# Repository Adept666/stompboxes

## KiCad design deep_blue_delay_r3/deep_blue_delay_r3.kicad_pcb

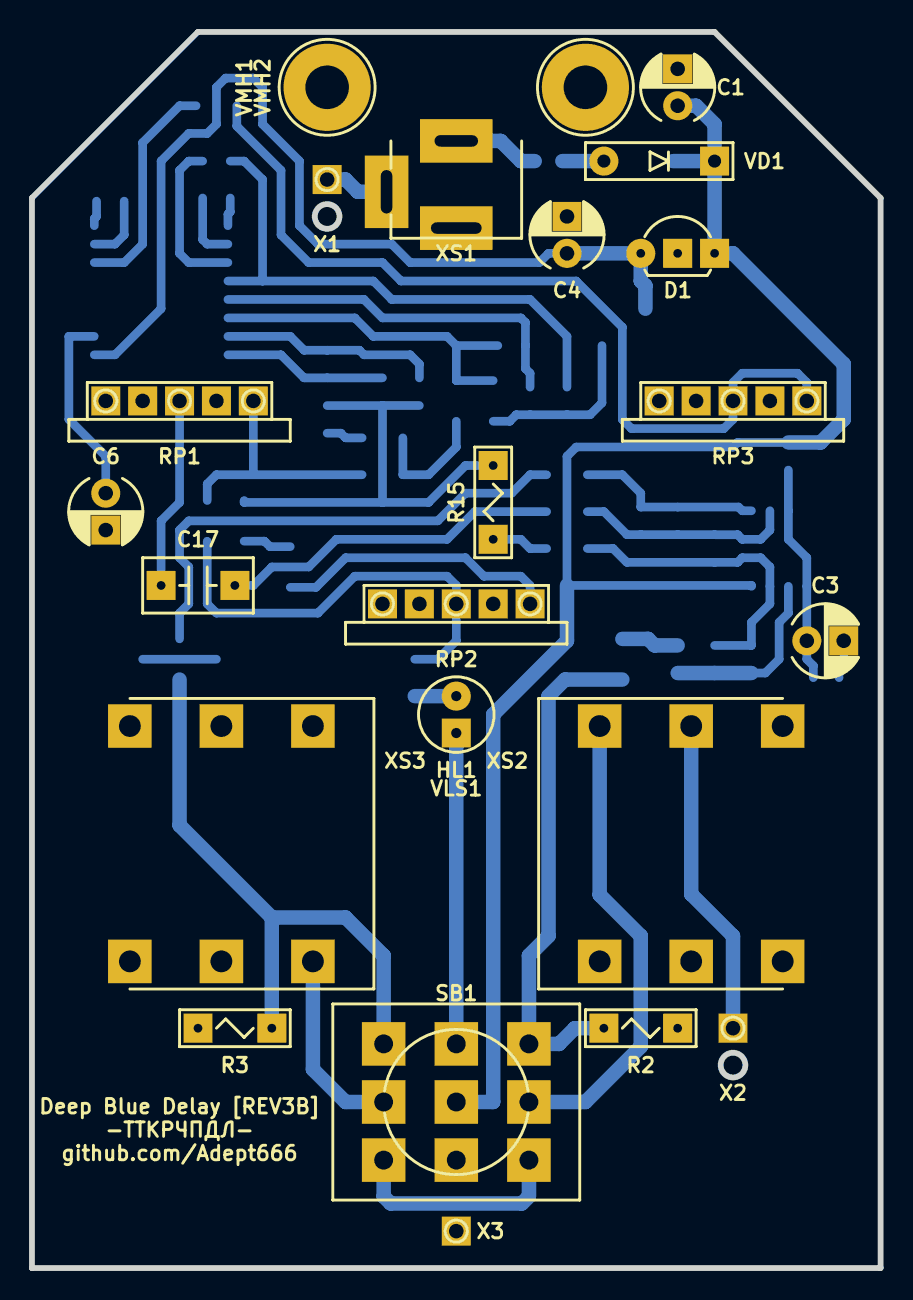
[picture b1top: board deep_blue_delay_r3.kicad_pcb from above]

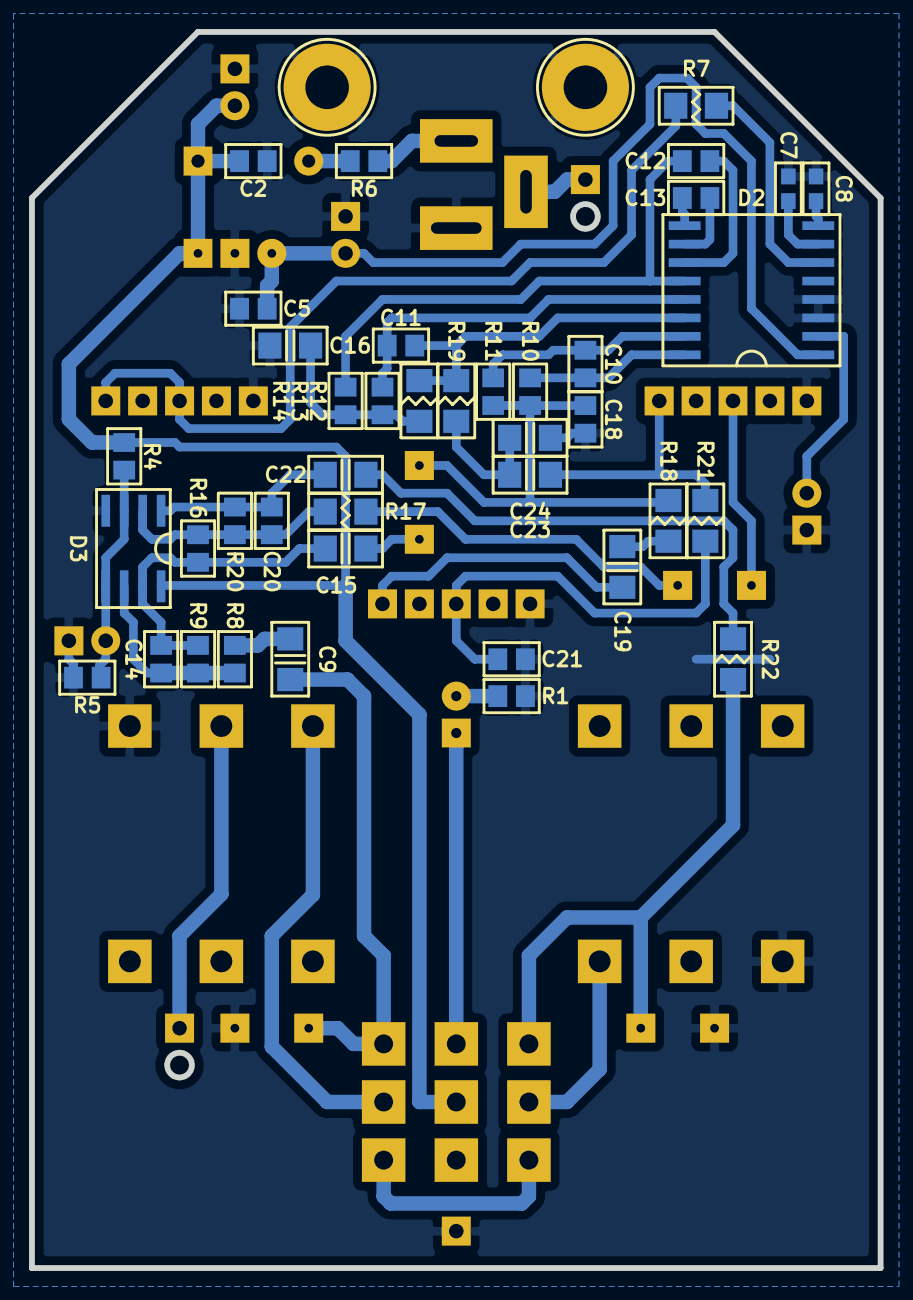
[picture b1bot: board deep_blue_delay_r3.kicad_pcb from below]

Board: 2 copper layers, 58.4 x 85.1 mm, 66 parts (40 on the bottom side), 44 nets.

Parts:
C1: 107; CP-RADIAL-D05.0-P02.0-CLS
C2, C5, C12, C13: 104; C-SM-0805
C3, C4, C6: 476; CP-RADIAL-D05.0-P02.0-CLS
C7, C8: 104; C-SM-0603
C9, C19: 223; C-SM-1206
C10, C11: 222; C-SM-0805
C14: 470; C-SM-0805
C15, C22, C23: 105; C-SM-1206
C16: 153; C-SM-1206
C17: 105; C-DISK-D04.2-T03.0-P05.08-d0.5
C18: 472; C-SM-0805
C20: 101; C-SM-0805
C21: 473; C-SM-0805
C24: 103; C-SM-1206
D1: 78L05; P-TO-92-OUT-GND-IN
D2: 8970; P-SO-16W
D3: 5532; P-SO-08
GB1: PP3; B-PP3-HV
HL1: FYL-5013UWC; LED-ROUND-05.0-UNI-SH-SPACER
R1, R4, R5, R10, R11, R13, R14: 103; R-SM-0805
R2: 105; R-MFR-12
R3: 104; R-MFR-12
R6: 330; R-SM-0805
R7: 272; R-SM-1206
R8: 184; R-SM-0805
R9: 364; R-SM-0805
R12, R17: 203; R-SM-1206
R15: 103; R-MFR-12
R16: 223; R-SM-0805
R18: 512; R-SM-1206
R19, R22: 102; R-SM-1206
R20: 123; R-SM-0805
R21: 202; R-SM-1206
RP1, RP2, RP3: B50K; RP-PDB181-K-F-PCB-RND
SB1: PBS-24-302SP; SW-PBS-24-302SP
VD1: 5817; P-DO-41
VE1: B013; B013_deep_blue_delay_r3a
VLS1: BR-17.8; VLS-BR
VMH1, VMH2: DI5M3x20; VMH-STA-DA5
X1: +; CON-PAD-S-1.0-2.0
X2: -; CON-PAD-S-1.0-2.0
X3: COM; CON-PAD-S-1.0-2.0
XS1: DC-005; CON-DC-005
XS2, XS3: PJ-644C; CON-PJ-644C

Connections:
/IN-CON: SB1.COM3, XS2.T
/IN-SCH: C9.1, R2.2, SB1.NO3
/LED: HL1.A, SB1.NO2
/OUT-CON: SB1.COM1, XS3.T
/OUT-SCH: R3.2, R22.2, SB1.NO1
/PP3-NEG: X2.1, XS2.R
/PP3-POS: X1.1, XS1.SN
COM: C1.-, C2.2, C3.-, C4.-, C5.2, C6.-, C7.1, C8.1, C16.2, C18.2, C21.2, C24.2, D1.GND, D2.3, D2.4, D3.4, R1.1, R2.1, R3.1, R5.1, RP1.1, RP2.1, RP3.1, VMH1.0, VMH2.0, X3.1, XS1.C, XS2.S, XS3.S
unnamed: C6.+, D2.2
unnamed: C7.2, D2.7
unnamed: C8.2, D2.8
unnamed: C9.2, R8.1
unnamed: C10.1, D2.16, R10.1
unnamed: C10.2, D2.15, R11.1
unnamed: C11.1, D2.14, R12.1, R19.1
unnamed: C11.2, D2.13, R13.1
unnamed: C12.1, D2.12, R14.1
unnamed: C12.2, D2.11
unnamed: C13.1, D2.10
unnamed: C13.2, D2.9
unnamed: C14.1, D3.6, R8.2, R9.1
unnamed: C14.2, C15.1, D3.7, R9.2, R16.1
unnamed: C15.2, R15.2
unnamed: C16.1, R12.2, R13.2, R14.2
unnamed: C17.1, R17.1
unnamed: C17.2, RP1.2
unnamed: C18.1, R10.2, R11.2, R15.1, R18.2
unnamed: C19.1, R18.1
unnamed: C19.2, RP2.3
unnamed: C20.1, D3.2, R16.2, R17.2, R20.1
unnamed: C20.2, C22.1, D3.1, R20.2
unnamed: C21.1, R21.1, RP2.2
unnamed: C22.2, R22.1
unnamed: C23.1, R21.2, RP1.3
unnamed: C23.2, C24.1, R19.2
unnamed: D2.6, R7.2
unnamed: HL1.C, R1.2
unnamed: R6.1, XS1.S
unnamed: R6.2, VD1.A
unnamed: R7.1, RP3.2, RP3.3
unnamed: SB1.NC1, SB1.NC3
V: C1.+, C2.1, D1.IN, D3.8, R4.2, SB1.COM2, VD1.C
VA: C4.+, C5.1, D1.OUT, D2.1
VB: C3.+, D3.3, D3.5, R4.1, R5.2

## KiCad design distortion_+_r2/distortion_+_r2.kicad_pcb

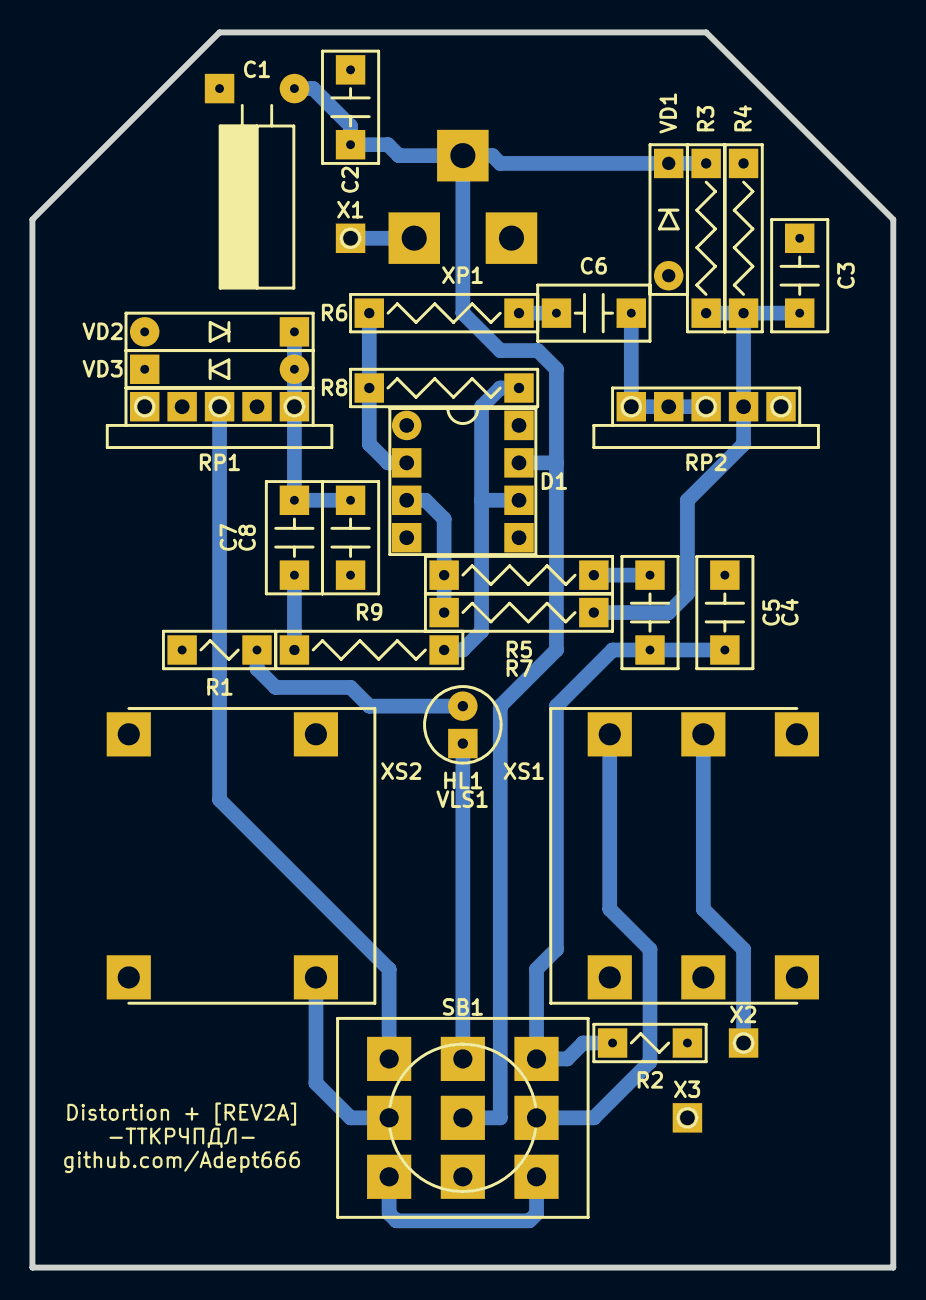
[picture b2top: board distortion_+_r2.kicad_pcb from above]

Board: 2 copper layers, 58.4 x 83.8 mm, 34 parts (0 on the bottom side), 20 nets.

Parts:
C1: 107; CP-RADIAL-D05.0-P02.0-d0.5-L11-HU
C2: 104; C-DISK-D04.2-T03.0-P05.08-d0.5
C3, C7: 105; C-DISK-D04.2-T03.0-P05.08-d0.5
C4, C8: 102; C-DISK-D04.2-T03.0-P05.08-d0.5
C5: 103; C-DISK-D04.2-T03.0-P05.08-d0.5
C6: 473; C-DISK-D04.2-T03.0-P05.08-d0.5
D1: 741; P-DIP-08
GB1: PP3; B-PP3-HV
HL1: FYL-5013UWC; LED-ROUND-05.0-UNI-SH-SPACER
R1: 103; R-MFR-12
R2: 105; R-MFR-12
R3, R4, R7, R8: 105; R-MFR-25
R5, R9: 103; R-MFR-25
R6: 472; R-MFR-25
RP1: A10K; RP-PDB181-K-F-PCB
RP2: C1M; RP-PDB181-K-F-PCB
SB1: PBS-24-302SP; SW-PBS-24-302SP
VD1: 400x; P-DO-41
VD2, VD3: 34A; P-DO-7
VE1: B013; B013_distortion_+_r2a
VLS1: BR-17.8; VLS-BR
X1: +; CON-PAD-S-1.0-2.0
X2: -; CON-PAD-S-1.0-2.0
X3: COM; CON-PAD-S-1.0-2.0
XP1: 722RA; CON-(L)7X2RA(H)
XS1: NYS215; CON-NYS-215
XS2: NYS2152; CON-NYS-2152

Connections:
/IN-CON: SB1.COM3, XS1.T
/IN-SCH: C4.1, C5.1, R2.2, SB1.NO3
/LED: HL1.A, SB1.NO2
/OUT-CON: SB1.COM1, XS2.T
/OUT-SCH: RP1.2, SB1.NO1
/PP3-NEG: X2.1, XS1.R
/PP3-POS: X1.1, XP1.SN
COM: C1.-, C2.2, C3.2, C4.2, C8.2, D1.4, R1.1, R2.1, R4.1, RP1.1, RP1.NC2, RP2.3, VD1.A, VD2.A, VD3.C, X3.1, XP1.C, XS1.S, XS2.S
unnamed: C5.2, R5.1
unnamed: C6.1, RP2.1, RP2.2, RP2.NC1
unnamed: C6.2, R6.1
unnamed: C7.1, R9.2
unnamed: C7.2, C8.1, RP1.3, VD2.C, VD3.A
unnamed: D1.2, R6.2, R8.1
unnamed: D1.3, R5.2, R7.1
unnamed: D1.6, R8.2, R9.1
unnamed: HL1.C, R1.2
unnamed: SB1.NC1, SB1.NC3
V: C1.+, C2.1, D1.7, R3.2, SB1.COM2, VD1.C, XP1.S
VA: C3.1, R3.1, R4.2, R7.2, RP2.NC2

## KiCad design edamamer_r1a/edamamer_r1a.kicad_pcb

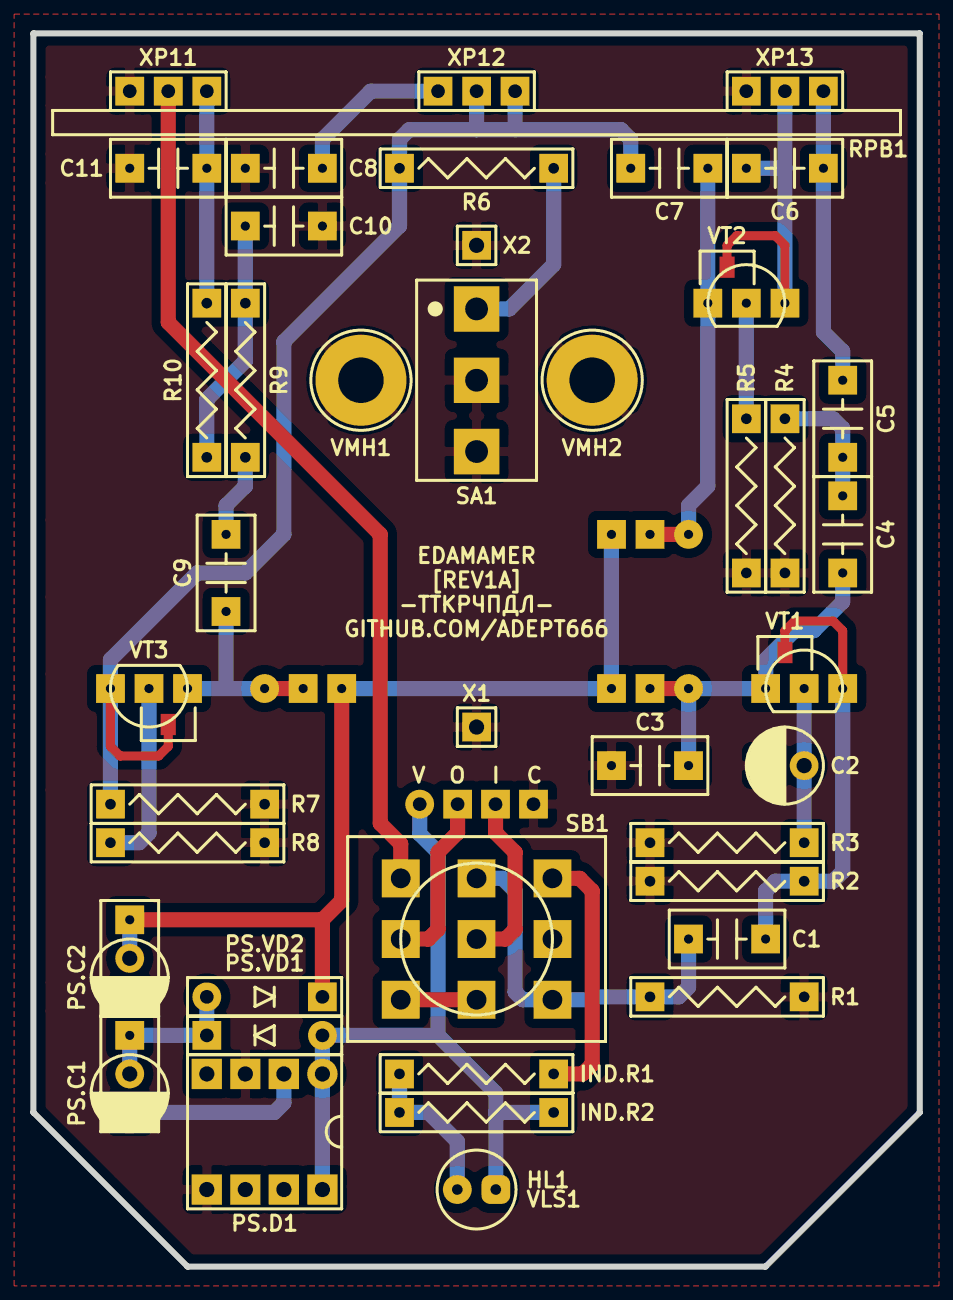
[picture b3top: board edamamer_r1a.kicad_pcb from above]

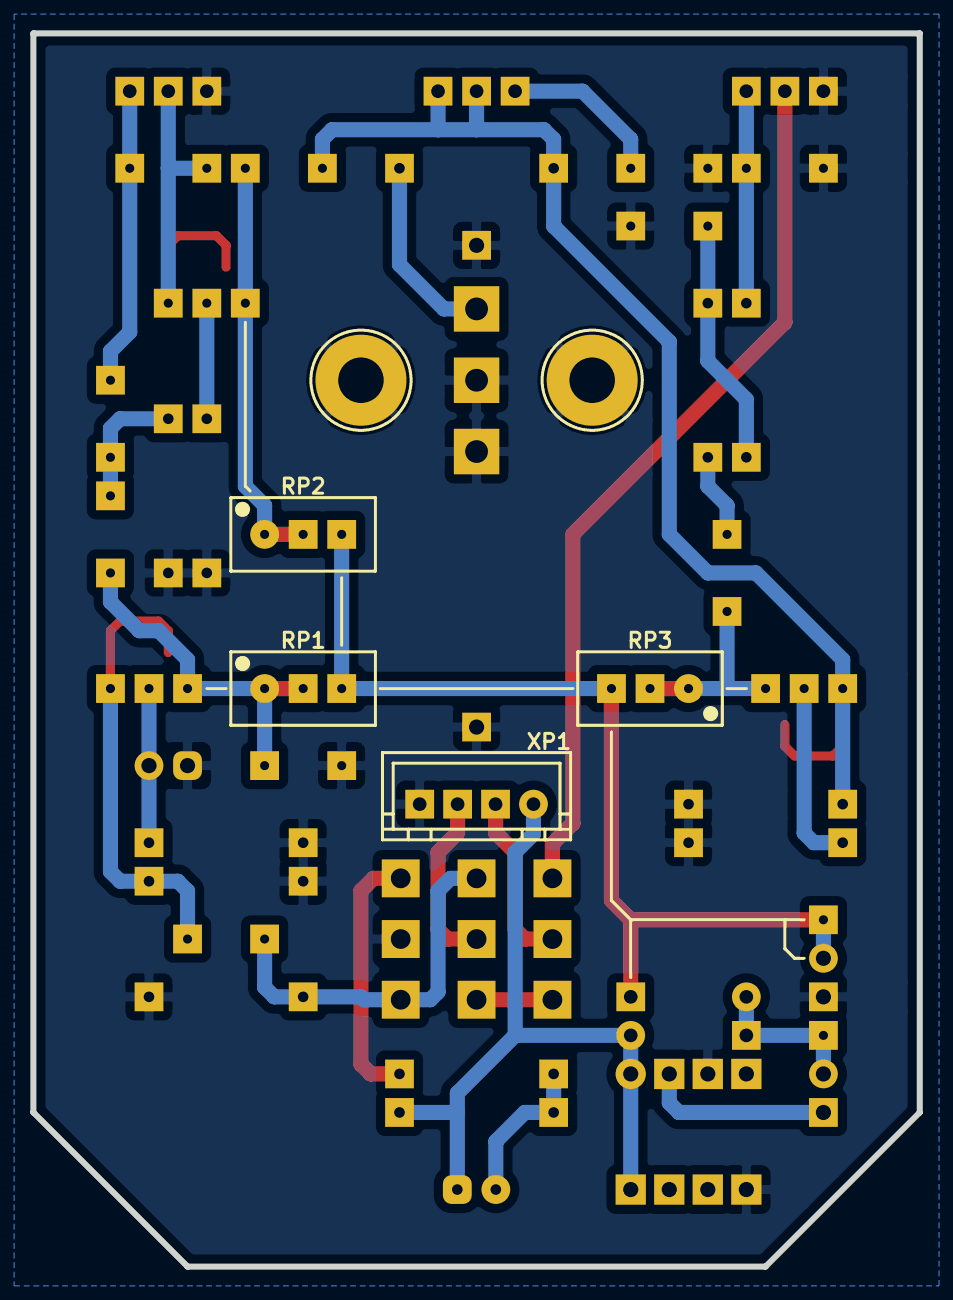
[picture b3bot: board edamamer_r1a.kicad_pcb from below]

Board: 2 copper layers, 58.4 x 81.3 mm, 46 parts (4 on the bottom side), 28 nets.

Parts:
C1: 223; C-DISK-D04.2-T03.0-P05.08-d0.5
C2: 336; CP-RADIAL-D05.0-P02.0-CLS
C3, C6: 471; C-DISK-D04.2-T03.0-P05.08-d0.5
C4, C5, C8: 472; C-DISK-D04.2-T03.0-P05.08-d0.5
C7, C9: 103; C-DISK-D04.2-T03.0-P05.08-d0.5
C10, C11: 332; C-DISK-D04.2-T03.0-P05.08-d0.5
HL1: FYL-5013URC; LED-ROUND-05.0-UNI-SH-SPACER-PNL-5.3
IND.R1: 472; R-MFR-25
IND.R2: X; R-MFR-25
PS.C1, PS.C2: 105; C-DISK-D04.2-T03.0-P05.08-d0.5-OR-CP-RADIAL-D05.0-P02.0-CLS
PS.D1: 7660S; P-DIP-08
PS.VD1, PS.VD2: 400x; P-DO-41
R1, R2: 105; R-MFR-25
R3: 152; R-MFR-25
R4, R7: 474; R-MFR-25
R5: 272; R-MFR-25
R6: 124; R-MFR-25
R8: 221; R-MFR-25
R9, R10: 123; R-MFR-25
RP1, RP2: 100K; RP-3296W
RP3: 50K; RP-3296W
RPB1: A100K-A500K-A500K; RPB-1590N1-18-3x17-1.6-PNL-7.4-2.8
SA1: MTS-102-A2; SW-MTS-102-A2-3.0-PNL-6.0
SB1: PBS-24-302SP; SW-PBS-24-302SP-2.5-PNL-13.0
VE1: 1590N1; 1590N1_A1
VLS1: BR-12.7; VLS-BR
VMH1, VMH2: DI5M3x18; VMH-STA-DA5-PNL-3.0
VT1, VT2: J201; P-SOT-23-D-S-G-OR-TO-92-D-S-G
VT3: 5457; P-SOT-23-D-S-G-OR-TO-92-D-S-G
X1, X2: COM; CON-PAD-S-1.0-1.9
XB1: 1590N1 Connector Board; XB-1590N1
XP1: B4B-XH-A; CON-XH-B4B-A

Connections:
/IN-CIR: C1.1, R1.2, SB1.NC3, SB1.NO2
/IN-CON: SB1.COM2, XP1.3
/LED: IND.R1.1, SB1.NO3
/OUT-CIR: RPB1.12, SB1.NO1
/OUT-CON: SB1.COM1, XP1.2
COM: C2.-, C3.2, C8.2, C10.2, C11.2, PS.C2.-, PS.D1.3, PS.D1.5, R1.1, R2.1, R3.1, R4.1, R5.1, R7.1, R8.1, RPB1.11, RPB1.31, SA1.COM, SA1.NO, SB1.COM3, VMH1.0, VMH2.0, X1.1, X2.1, XP1.4
unnamed: C1.2, R2.2, VT1.G
unnamed: C2.+, R3.2, VT1.S
unnamed: C3.1, C4.1, RP1.1, RP1.2, VT1.D
unnamed: C4.2, C5.1, R4.2
unnamed: C5.2, C6.1, RPB1.33
unnamed: C6.2, RPB1.32, VT2.G
unnamed: C7.1, RP2.1, RP2.2, VT2.D
unnamed: C7.2, R6.2, R7.2, RPB1.22, RPB1.23, VT3.G
unnamed: C8.1, RPB1.21
unnamed: C9.1, RP3.1, RP3.2, VT3.D
unnamed: C9.2, R9.1
unnamed: C10.1, R9.2, R10.1
unnamed: C11.1, R10.2, RPB1.13
unnamed: HL1.C, IND.R1.2, IND.R2.1
unnamed: PS.C1.+, PS.VD1.C, PS.VD2.A
unnamed: PS.C1.-, PS.D1.2
unnamed: R5.2, VT2.S
unnamed: R6.1, SA1.NC
unnamed: R8.2, VT3.S
unnamed: SB1.NC1, SB1.NC2
V: HL1.A, IND.R2.2, PS.D1.1, PS.D1.8, PS.VD1.A, XP1.1
VA: PS.C2.+, PS.VD2.C, RP1.3, RP2.3, RP3.3

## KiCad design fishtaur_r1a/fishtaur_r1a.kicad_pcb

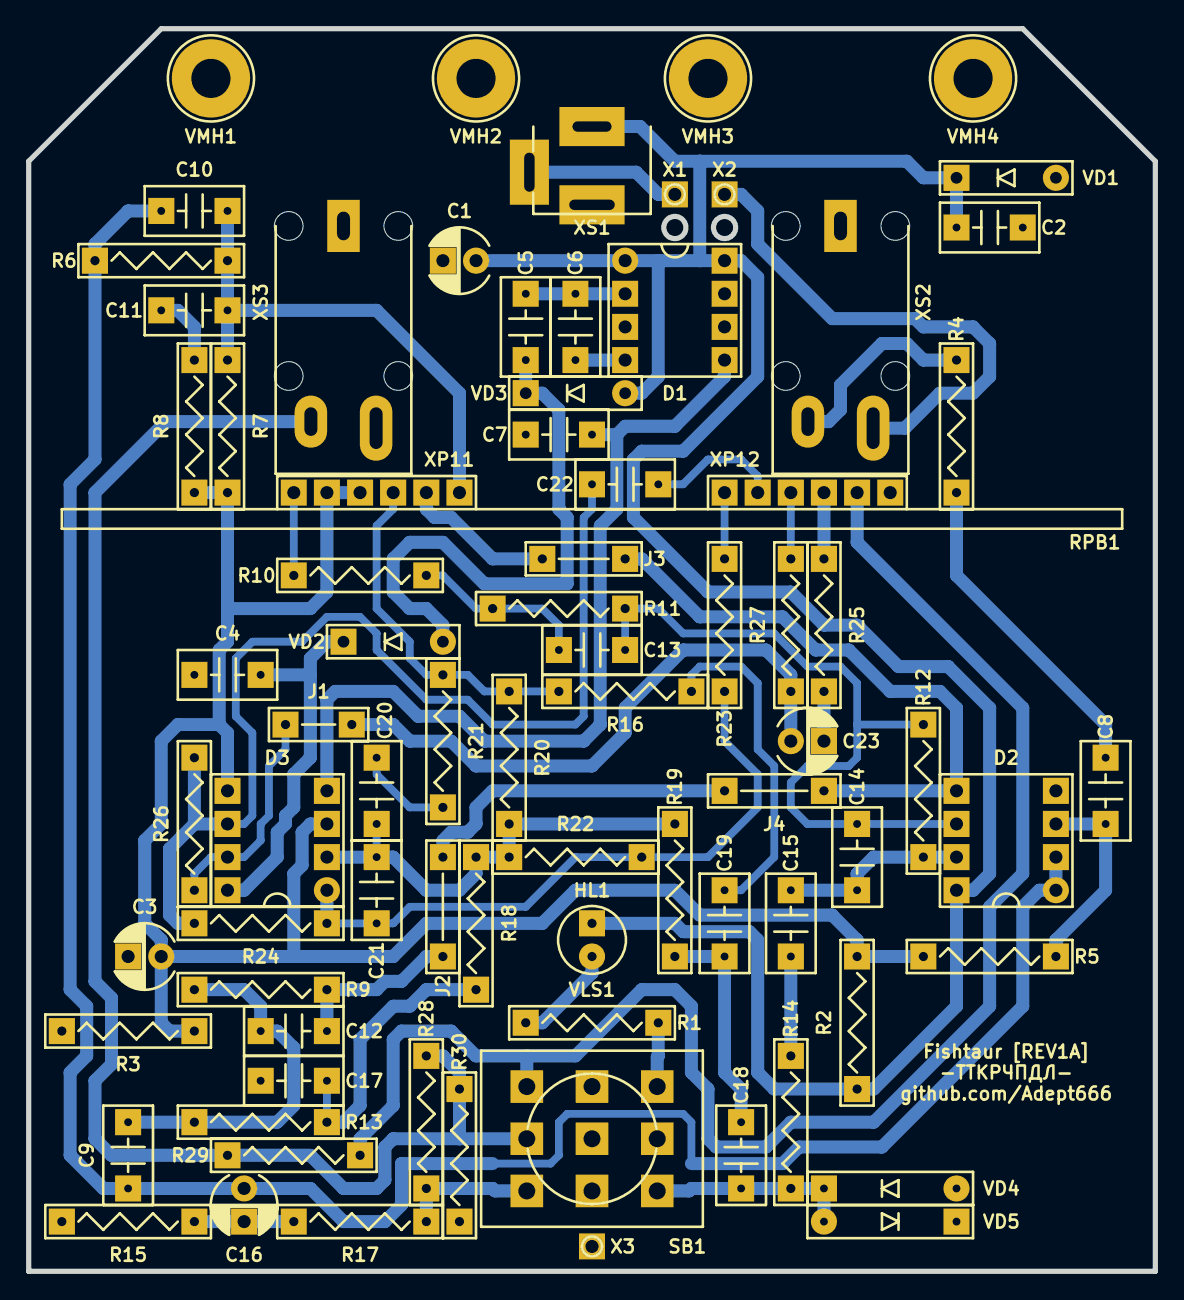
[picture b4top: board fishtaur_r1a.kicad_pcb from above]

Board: 2 copper layers, 86.4 x 95.3 mm, 81 parts (0 on the bottom side), 44 nets.

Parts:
C1, C3: 476; CP-RADIAL-D05.0-P02.0-CLS
C2, C8, C9: 104; C-DISK-D04.2-T03.0-P05.08-d0.5
C4, C5, C6, C7, C15, C17, C18: 105; C-DISK-D04.2-T03.0-P05.08-d0.5
C10, C12: 683; C-DISK-D04.2-T03.0-P05.08-d0.5
C11: 334; C-DISK-D04.2-T03.0-P05.08-d0.5
C13: 823; C-DISK-D04.2-T03.0-P05.08-d0.5
C14: 391; C-DISK-D04.2-T03.0-P05.08-d0.5
C16, C23: 475; CP-RADIAL-D05.0-P02.0-CLS
C19: 222; C-DISK-D04.2-T03.0-P05.08-d0.5
C20: 223; C-DISK-D04.2-T03.0-P05.08-d0.5
C21: 821; C-DISK-D04.2-T03.0-P05.08-d0.5
C22: 392; C-DISK-D04.2-T03.0-P05.08-d0.5
D1: 7660S; P-DIP-08
D2, D3: 072; P-DIP-08
GB1: PP3; B-PP3-HV
HL1: FYL-5013UWC; LED-ROUND-05.0-UNI-SH-SPACER-PNL-5.3
J1: 0.6; J-TH-d0.6-P05.08
J2, J4: 0.6; J-TH-d0.6-P07.62
J3: 0.6; J-TH-d0.6-P06.35
R1, R4, R9: 103; R-MFR-25
R2, R3, R20: 273; R-MFR-25
R5: 105; R-MFR-25
R6: 512; R-MFR-25
R7, R13: 152; R-MFR-25
R8, R14: 102; R-MFR-25
R10: 202; R-MFR-25
R11, R18: 153; R-MFR-25
R12: 434; R-MFR-25
R15, R24, R26, R30: 104; R-MFR-25
R16: 223; R-MFR-25
R17, R25: 561; R-MFR-25
R19: 473; R-MFR-25
R21: 123; R-MFR-25
R22: 394; R-MFR-25
R23: 182; R-MFR-25
R27: 472; R-MFR-25
R28, R29: 683; R-MFR-25
RPB1: B100K-B10K-B10K; RPB-1590BB-18-3x17-DUAL-SINGLE-SINGLE-1.5-PNL-7.4-2.8
SB1: PBS-24-302SP; SW-PBS-24-302SP-2.5-PNL-13.0
VD1: 4742A; P-DO-41
VD2, VD3: 400x; P-DO-41
VD4, VD5: 34A; P-DO-7
VE1: 1590BB; 1590BB_B1
VLS1: BR-12.7; VLS-BR
VMH1, VMH2, VMH3, VMH4: DI5M3x18; VMH-STA-DA5-PNL-3.0
X1: +; CON-PAD-S-1.0-2.0
X2: -; CON-PAD-S-1.0-2.0
X3: COM; CON-PAD-S-1.0-2.0
XS1: DC-005; CON-DC-005
XS2: ST-008S-04; CON-ST-008X-04-OR-ST-008X-05
XS3: ST-008S-05; CON-ST-008X-04-OR-ST-008X-05

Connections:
/BYPASS: R17.2, R28.1, SB1.NC1
/EFFECT: R29.1, RPB1.32, SB1.NO1
/IN: R4.1, XS2.T
/J1: C23.+, D3.7, J1.J, R26.2, R27.2
/J2: C12.2, D2.5, J2.J, J3.J, J4.J, R9.2, RPB1.11
/LED: R1.1, SB1.NO3
/LED-CIR: C18.1, R14.2, SB1.NC3, VD4.C, VD5.A
/OUT: R28.2, R29.2, R30.2, SB1.COM1, XS3.T
/PP3-NEG: X2.1, XS2.R/TN
/PP3-POS: X1.1, XS1.SN
COM: C1.-, C2.2, C3.-, C4.2, C7.1, C17.2, D1.3, D2.4, R3.1, R15.1, R30.1, RPB1.31, SB1.COM2, SB1.COM3, SB1.NC2, VD1.A, VD4.A, VD5.C, VMH1.0, VMH2.0, VMH3.0, VMH4.0, X3.1, XS1.C, XS2.S, XS3.S
unnamed: C5.1, VD2.A, VD3.C
unnamed: C5.2, C6.1, D1.2
unnamed: C6.2, D1.4
unnamed: C8.1, R4.2
unnamed: C8.2, D2.3, R5.2
unnamed: C9.1, C10.1, C16.+, D2.1, D2.2, R6.2
unnamed: C10.2, C11.1, R6.1, R7.2, RPB1.14
unnamed: C11.2, R8.2
unnamed: C9.2, C12.1, R9.1, R13.1
unnamed: C13.1, R10.1, R11.1
unnamed: C13.2, C14.1, D2.6, R11.2, R12.1
unnamed: C14.2, C15.1, D2.7, R12.2
unnamed: C15.2, R14.1
unnamed: C16.-, R15.2, R17.1
unnamed: C17.1, R13.2, R18.1
unnamed: C18.2, C19.1, R19.1
unnamed: C19.2, R16.2
unnamed: C20.1, C21.1, D3.2, R18.2, R19.2, R20.2, R22.1
unnamed: C20.2, R21.2
unnamed: C21.2, D3.1, R22.2, R23.1, R24.1
unnamed: C22.1, RPB1.22
unnamed: C22.2, D3.6, R24.2, R26.1
unnamed: C23.-, R25.1
unnamed: HL1.C, R1.2
unnamed: R10.2, RPB1.13
unnamed: R16.1, R20.1, R21.1, RPB1.15
unnamed: R23.2, RPB1.23
unnamed: R25.2, RPB1.33
unnamed: R27.1, RPB1.21
VA: C1.+, C2.1, D1.1, D1.8, D2.8, HL1.A, R2.2, VD1.C, VD3.A, XS1.S
VB: C4.1, D3.8, VD2.C
VC: C7.2, D1.5, D3.4
VREF: C3.+, D3.3, D3.5, R2.1, R3.2, R5.1, R7.1, R8.1, RPB1.12, RPB1.16

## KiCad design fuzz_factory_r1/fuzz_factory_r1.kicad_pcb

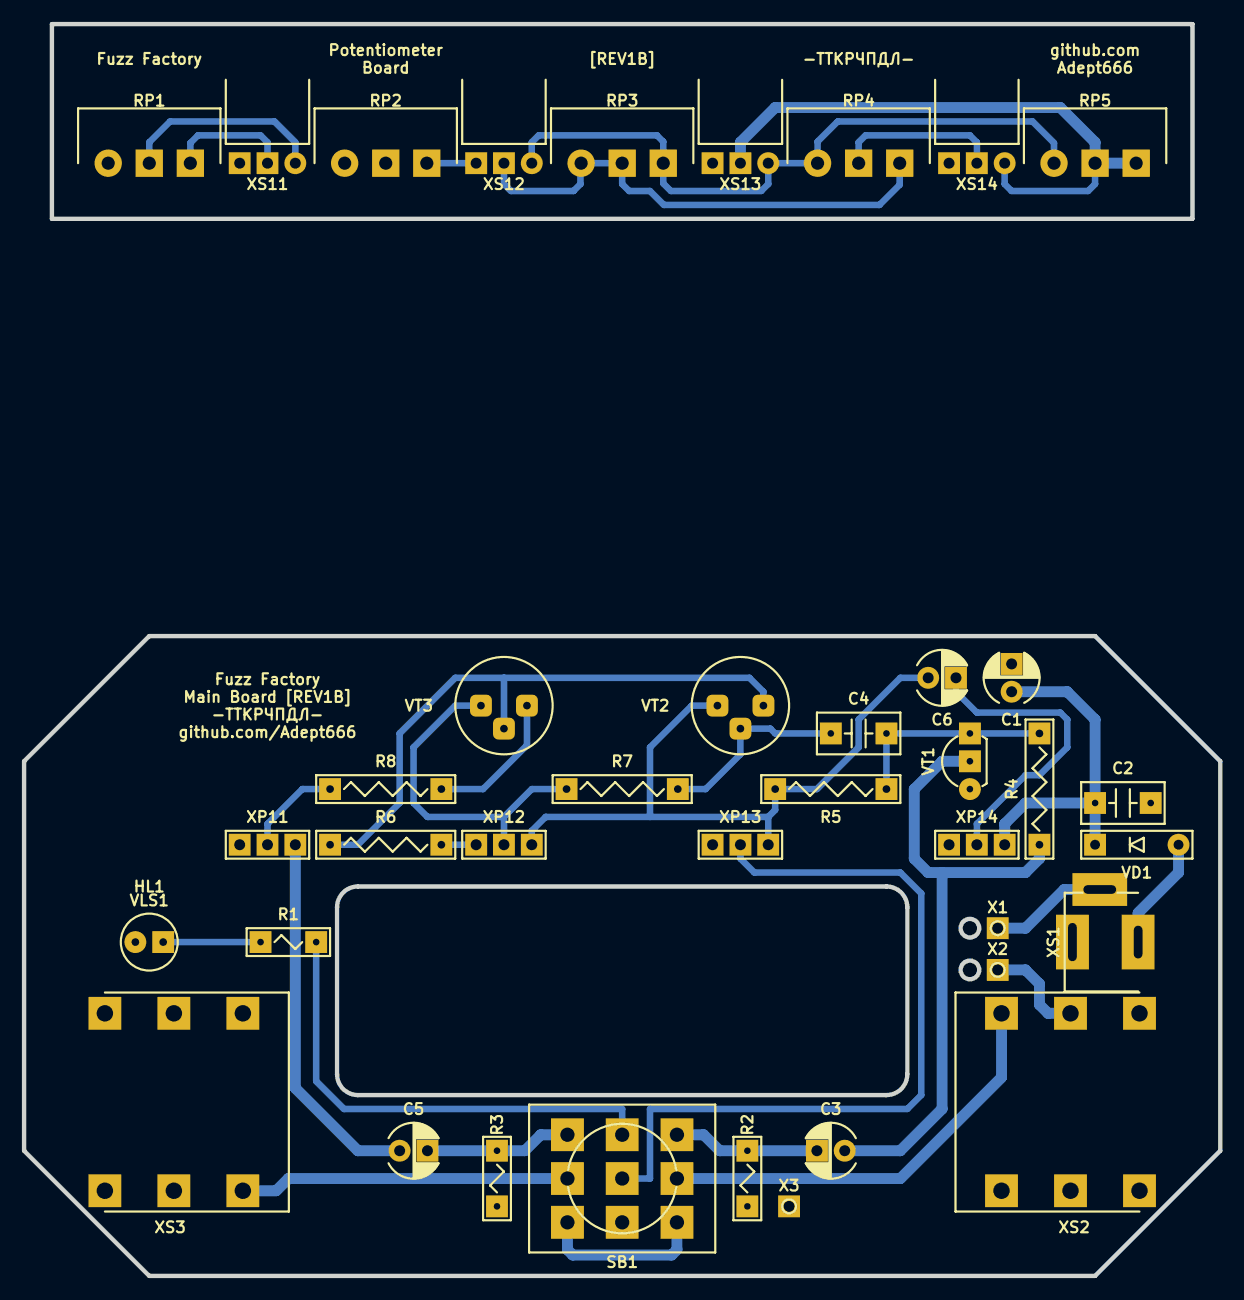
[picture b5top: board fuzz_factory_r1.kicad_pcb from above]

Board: 2 copper layers, 109.2 x 114.3 mm, 42 parts (0 on the bottom side), 31 nets.

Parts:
C1: 107; CP-RADIAL-D05.0-P02.0-CLS
C2, C4: 104; C-DISK-D04.2-T03.0-P05.08-d0.5
C3, C5, C6: 106; CP-RADIAL-D05.0-P02.0-CLS
GB1: PP3; B-PP3-HV
HL1: FYL-5013UWC; LED-ROUND-05.0-UNI-SH-SPACER
R1: 103; R-MFR-12
R2: 105; R-MFR-12
R3: 224; R-MFR-12
R4: 224; R-MFR-25
R5: 103; R-MFR-25
R6: 471; R-MFR-25
R7: 473; R-MFR-25
R8: 512; R-MFR-25
RP1, RP5: B5K; RP-RK1233N1-L15-KC
RP2, RP3, RP4: B10K; RP-RK1233N1-L15-KC
SB1: PBS-24-302SP; SW-PBS-24-302SP
VD1: 5817; P-DO-41
VE1: B013; B013_fuzz_factory_r1a
VLS1: BR-17.8; VLS-BR
VT1: 3904; P-TO-92-E-B-C
VT2, VT3: МП40; P-КТЮ-3-6
X1: +; CON-PAD-S-1.0-2.0
X2: -; CON-PAD-S-1.0-2.0
X3: COM; CON-PAD-S-1.0-2.0
XP11, XP12, XP13, XP14: PLS-03; CON-PLS-03
XS1: DC-005; CON-DC-005
XS2, XS3: PJ-644C; CON-PJ-644C
XS11, XS12, XS13, XS14: PBS-03R; CON-PBS-03R

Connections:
/IN-CON: SB1.COM3, XS2.T
/IN-SCH: C3.-, R2.2, SB1.NO3
/LED: R1.2, SB1.NO2
/MB1: R8.1, XP11.2
/MB2: C5.+, XP11.1
/MB3: R6.1, XP12.3
/MB4: R7.2, VT3.E, XP12.2
/MB5: C6.+, R5.2, VT2.E, XP12.1, XP13.1
/MB7: C6.-, XP14.2
/OUT-CON: SB1.COM1, XS3.T
/OUT-SCH: C5.-, R3.2, SB1.NO1
/PB1: RP1.3, XS11.2
/PB2: RP1.2, XS11.1
/PB3: RP2.3, XS12.3
/PB4: RP3.1, RP3.2, RP4.3, XS12.2
/PB5: RP3.3, RP4.1, RP5.1, XS12.1, XS13.1
/PB7: RP4.2, XS14.2
/PBCOM: RP1.1, RP2.1, RP2.2, XS11.3, XS13.3, XS14.3
/PBV: RP5.2, RP5.3, XS13.2, XS14.1
/PP3-NEG: X2.1, XS2.R
/PP3-POS: X1.1, XS1.SN
COM: C1.-, C2.2, HL1.C, R2.1, R3.1, VT1.E, X3.1, XP11.3, XP14.3, XS1.C, XS2.S, XS3.S
unnamed: C3.+, R4.1, VT1.B
unnamed: C4.1, R4.2, R5.1, VT1.C
unnamed: C4.2, R7.1, VT2.B
unnamed: HL1.A, R1.1
unnamed: R6.2, VT2.C, VT3.B
unnamed: R8.2, VT3.C
unnamed: SB1.NC1, SB1.NC3
unnamed: VD1.A, XS1.S
V: C1.+, C2.1, SB1.COM2, VD1.C, XP13.2, XP14.1

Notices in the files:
deep_blue_delay_r3/deep_blue_delay_r3.kicad_pcb:
This project is licensed under GNU General Public License v3.0 or later
